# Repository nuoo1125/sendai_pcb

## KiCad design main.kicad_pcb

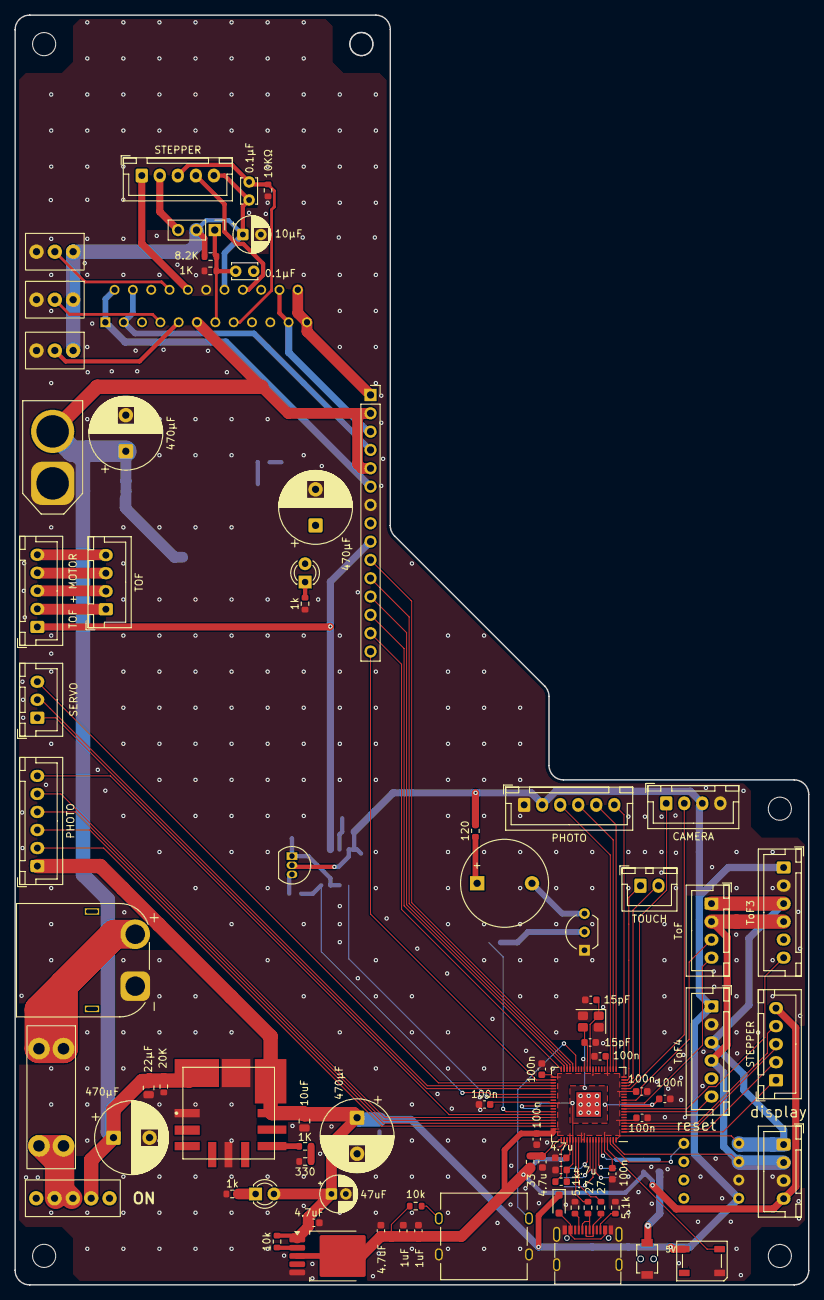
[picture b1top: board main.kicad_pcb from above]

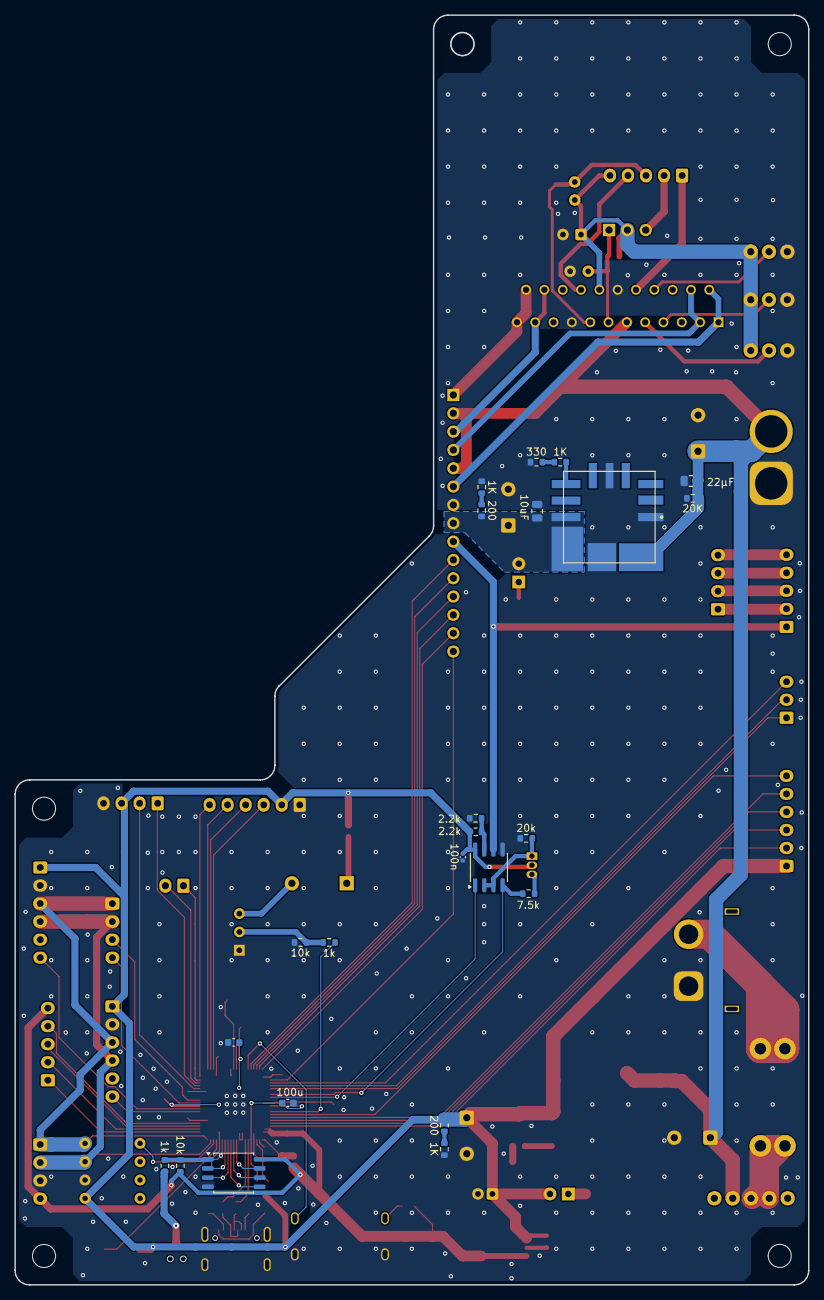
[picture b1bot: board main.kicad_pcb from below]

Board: 2 copper layers, 110.0 x 176.0 mm, 105 parts (23 on the bottom side), 97 nets.

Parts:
1K: 1K; R_0603_1608Metric
330: 330; R_0603_1608Metric
BZ1: UDB-05LFPN; Buzzer_12x9.5RM7.6
C1: 47uF; CP_Radial_D5.0mm_P2.00mm
C2, C3, C18, C19: 470μF; CP_Radial_D10.0mm_P5.00mm
C4, C8: 0.1μF; C_Disc_D3.4mm_W2.1mm_P2.50mm
C5, C9: 4.7uF; C_0603_1608Metric
C6, C7: 22μF; C_0805_2012Metric
C10, C13: 1uF; C_0603_1608Metric
C11: 100n; C_0402_1005Metric
C12: 10μF; CP_Radial_D5.0mm_P2.50mm
C14, C17, C20, C21: 4.7u; C_0603_1608Metric
C15, C16: 10uF; C_0805_2012Metric
C22, C23: 15pF; C_0603_1608Metric
C24: 100u; C_0603_1608Metric
C25, C26, C27, C28, C29, C30, C31, C32: 100n; C_0603_1608Metric
D1: CUHS20S30; D_SOD-323_HandSoldering
D2, D4: LED; LED_D3.0mm
D3: WS2812B; LED_WS2812B_PLCC4_5.0x5.0mm_P3.2mm
F1: Fuse; 3557-15_fuseholder
J1: Conn_01x02_Pin; AMASS_XT60PW-M_1x02_P7.20mm_Horizontal
J2: RP2350; USB_C
J5: Conn_01x04; JST_XH_B4B-XH-A_1x04_P2.50mm_Vertical
J6: ToF3; JST_XH_B6B-XH-A_1x06_P2.50mm_Vertical
J7: ToF4; JST_XH_B6B-XH-A_1x06_P2.50mm_Vertical
J8: ToF; JST_XH_B4B-XH-A_1x04_P2.50mm_Vertical
J9: gyro; bno055
J10: TOUCH; JST_XH_B2B-XH-A_1x02_P2.50mm_Vertical
J11, J12: PHOTO; JST_XH_B6B-XH-A_1x06_P2.50mm_Vertical
J15: Conn_01x02_Pin; AMASS_XT60-M_1x02_P7.20mm_Vertical
J16: TOF; JST_XH_B4B-XH-A_1x04_P2.50mm_Vertical
J17: CAMERA; JST_XH_B4B-XH-A_1x04_P2.50mm_Vertical
J18: Conn_01x15; PinSocket_1x15_P2.54mm_Vertical
L1: MBKK1608T3R3M; L_0603_1608Metric
MD1, MD2: OKL-T_6-W12N-C; MURATA_OKL-T-6-W12N-C_0
Q1: 2SA1015; TO-92_Inline
Q2: 2SC1815; PinHeader_1x03_P2.54mm_Vertical
Q3: 2N7000; TO-92_Inline_Wide
R1: 7.5k; R_0603_1608Metric
R2: 20k; R_0603_1608Metric
R3, R4: 5.1k; R_0603_1608Metric
R5, R6: 20K; R_0603_1608Metric
R7: 10KΩ; R_0603_1608Metric
R8, R10, R28, R31: 10k; R_0603_1608Metric
R9, R11, R27, R30: 1k; R_0603_1608Metric
R12: 8.2K; R_0603_1608Metric
R13, R16, R22, R23: 1K; R_0603_1608Metric
R14, R15: 2.2k; R_0603_1608Metric
R18: 330; R_0603_1608Metric
R20, R21: 200; R_0603_1608Metric
R24: 33; R_0603_1608Metric
R25, R26: 27; R_0603_1608Metric
R29: 120; R_0603_1608Metric
SERVO: Conn_01x03; JST_XH_B3B-XH-A_1x03_P2.50mm_Vertical
STEPPER: Conn_01x05; JST_XH_B5B-XH-A_1x05_P2.50mm_Vertical
STEPPER#2: Conn_01x05; JST_XH_B5B-XH-A_1x05_P2.50mm_Vertical
SW1: SW_SPDT; toggleswitch_tuyo
SW2: Boot_2350; TVAF06-A020B-R
SW3: SW_Push; takuto_sw
SW4, SW5, SW6: SW_SPDT; toggleswitch
TOF + MOTOR: Conn_01x05; JST_XH_B5B-XH-A_1x05_P2.50mm_Vertical
U1: NJM2819; TO-252-5_TabPin3
U2: MAX485ED; SOIC-8_3.9x4.9mm_P1.27mm
U3: W25Q128JVS; SOIC-8_5.3x5.3mm_P1.27mm
U4: SLA7078MPRT; sla7078
U5: RP2350_80QFN; RP2350-QFN-80-1EP_10x10_P0.4mm_EP3.4x3.4mm_ThermalVias
Y1: Crystal_GND24; Crystal_SMD_SeikoEpson_FA238-4Pin_3.2x2.5mm

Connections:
3.3V: C9.1, C10.1, C13.1, C14.1, C26.1, C27.1, C28.1, C29.1, C30.1, C31.1, C32.1, J5.4, R10.2, R24.1, R31.1, STEPPER#2.5, U1.3 (VOUT), U3.8 (VCC), U5.5 (IOVDD), U5.15 (IOVDD), U5.24 (IOVDD), U5.29 (IOVDD), U5.41 (IOVDD), U5.50 (IOVDD), U5.59 (ADC_AVDD), U5.60 (IOVDD), U5.64 (VREG_VIN), U5.68 (USB_OTP_VDD), U5.69 (QSPI_IOVDD), U5.76 (IOVDD)
3.3V_: C8.1, C12.1, Q2.2 (C), R12.1, STEPPER.5, SW4.1 (A), SW5.1 (A), SW6.1 (A), U4.14 (VDD)
+1V1: C17.1, C20.1, C24.1, C25.1, L1.1, U5.10 (DVDD), U5.32 (DVDD), U5.51 (DVDD), U5.65 (VREG_FB)
+5V: C1.1, C5.1, C11.1, C15.1, C18.1, D1.1 (K), D2.2 (A), D3.1 (VDD), J6.1, J7.1, J9.1, J11.2, J12.1, J17.3, MD1.4 (VOUT), MD1.5 (SENSE), Q1.2 (C), R8.1, R15.1, R20.1, R29.1, U1.1 (VIN), U2.8 (VCC)
+5VA: C16.1, C19.1, D4.2 (A), J18.8, MD2.4 (VOUT), MD2.5 (SENSE), R21.1
A: J18.6, U4.1 (OUTA), U4.2 (OUTA)
A_: J18.4, U4.3 (~OUTA), U4.4 (~OUTA)
B: J18.1, U4.22 (OUTB), U4.23 (OUTB)
B_: J18.3, U4.20 (~OUTB), U4.21 (~OUTB)
CS_2350: R9.2, R10.1, U3.1 (~CS), U5.75 (QSPI_SS)
DM_2350: J2.A7 (D-), J2.B7 (D-), R26.2
DP_2350: J2.A6 (D+), J2.B6 (D+), R25.2
GND: 330.1, C1.2, C2.2, C3.2, C4.2, C5.2, C6.2, C7.2, C9.2, C10.2, C11.2, C12.2, C13.2, C14.2, C15.2, C16.2, C17.2, C18.2, C19.2, C20.2, C21.2, C22.1, C23.1, C24.2, C25.2, C26.2, C27.2, C28.2, C29.2, C30.2, C31.2, C32.2, D3.3 (VSS), J1.1, J2.A1 (GND), J2.A12 (GND), J2.B1 (GND), J2.B12 (GND), J2.S1 (SHIELD), J5.3, J6.2, J7.2, J9.2, J11.1, J15.1, J17.4, J18.7, MD1.1 (~ON/OFF_CONTROL), MD1.3 (1_GROUND), MD1.7 (2_GROUND), MD2.1 (~ON/OFF_CONTROL), MD2.3 (1_GROUND), MD2.7 (2_GROUND), Q3.1 (S), R2.2, R3.2, R4.2, R5.1, R6.1, R7.2, R11.2, R13.2, R14.1, R18.1, R22.2, R23.2, R28.1, R30.2, SW2.1 (A), SW3.1, SW4.3 (C), SW5.3 (C), SW6.3 (C), U1.5 (GND), U2.5 (GND), U3.4 (GND), U4.12 (GND), U4.17 (SYNC), U5.62 (VREG_PGND), U5.81 (GND), Y1.2, Y1.4
M1: SW4.2 (B), U4.7 (M1)
M2: SW5.2 (B), U4.8 (M2)
M3: SW6.2 (B), U4.9 (M3)
unnamed: BZ1.1 (+), R29.2
unnamed: BZ1.2 (-), Q3.3 (D)
unnamed: D1.2 (A), J2.A4 (VBUS), J2.A9 (VBUS), J2.B4 (VBUS), J2.B9 (VBUS)
unnamed: D2.1 (K), R11.1
unnamed: D4.1 (K), R30.1
unnamed: F1.1, J1.2
unnamed: J2.A5 (CC1), R3.1
unnamed: J2.B5 (CC2), R4.1
unnamed: MD1.6 (TRIM), R16.2
unnamed: 1K.2, MD2.6 (TRIM)
unnamed: Q1.3 (B), R1.1
unnamed: Q1.1 (E), R2.1, U2.2 (~RE), U2.3 (DE)
unnamed: Q3.2 (G), R27.2, R28.2
unnamed: R16.1, R18.2
unnamed: 1K.1, 330.2
unnamed: R20.2, R22.1
unnamed: R21.2, R23.1
unnamed: F1.2, SW1.1 (A), SW1.2 (B)
unnamed: R9.1, SW2.2 (B)
unnamed: R8.2, U1.2 (CON)
unnamed: R14.2, R15.2, U2.7 (B)
unnamed: R31.2, SW3.2, U5.35 (RUN)
unnamed: R26.1, U5.66 (USB_DM)
unnamed: R25.1, U5.67 (USB_DP)
unnamed: C21.1, R24.2, U5.61 (VREG_AVDD)
unnamed: L1.2, U5.63 (VREG_LX)
unnamed: C22.2, U5.30 (XIN), Y1.1
unnamed: C23.2, U5.31 (XOUT), Y1.3
SCLK_2350: U3.6 (CLK), U5.71 (QSPI_SCLK)
SD0_2350: U3.5 (DI/IO_{0}), U5.72 (QSPI_SD0)
SD1_2350: U3.2 (DO/IO_{1}), U5.74 (QSPI_SD1)
SD2_2350: U3.3 (~WP/IO_{2}), U5.73 (QSPI_SD2)
SD3_2350: U3.7 (~HOLD/~RESET/IO_{3}), U5.70 (QSPI_SD3)
VCC: C2.1, C3.1, C6.1, C7.1, J15.2, J18.2, J18.5, MD1.2 (VIN), MD2.2 (VIN), R5.2, R6.2, SW1.3 (C), U4.11 (VBB)
buzaa: R27.1, U5.53 (GPIO42_ADC2)
camera_rx: J17.1, U5.17 (GPIO17)
camera_tx: J17.2, U5.16 (GPIO16)
clock: STEPPER#2.1, U5.1 (GPIO4)
clock_: STEPPER.1, U4.10 (CLOCK)
direction: STEPPER#2.4, U5.4 (GPIO7)
direction_: STEPPER.4, U4.16 (CW/CCW)
display_scl: J5.1, J6.3, J7.3, J8.1, J9.4, U5.80 (GPIO3)
display_sda: J5.2, J6.4, J7.4, J8.2, J9.3, U5.79 (GPIO2)
gyro_reset: J9.8, U5.78 (GPIO1)
ledfullcolor: D3.4 (DIN), U5.77 (GPIO0)
motor_rx: U2.1 (RO), U5.48 (GPIO39)
motor_serial: J18.9, TOF + MOTOR.1, U2.6 (A)
motor_tx: R1.2, U2.4 (DI), U5.47 (GPIO38)
obstacle_backward1: J12.6, U5.54 (GPIO43_ADC3)
obstacle_backward2: J12.5, U5.55 (GPIO44_ADC4)
obstacle_forward1: J10.2, U5.18 (GPIO18)
obstacle_forward2: J10.1, U5.19 (GPIO19)
photo_backward1: J12.4, U5.56 (GPIO45_ADC5)
photo_backward2: J12.3, U5.57 (GPIO46_ADC6)
photo_backward3: J12.2, U5.58 (GPIO47_ADC7)
photo_csn: J11.5, U5.21 (GPIO21)
photo_rx: J11.6, U5.20 (GPIO20)
photo_sck: J11.4, U5.22 (GPIO22)
photo_tx: J11.3, U5.23 (GPIO23)
reset: STEPPER#2.3, U5.3 (GPIO6)
reset_: C8.2, R7.1, STEPPER.3, U4.15 (RESET)
servo1: J18.15, U5.42 (GPIO33)
servo2: J18.14, U5.40 (GPIO32)
servo3: J18.13, U5.39 (GPIO31)
servo4: J18.12, U5.38 (GPIO30)
servo5: J18.11, U5.37 (GPIO29)
servo6: J18.10, U5.36 (GPIO28)
servo7: SERVO.3, U5.43 (GPIO34)
servo8: SERVO.2, U5.44 (GPIO35)
servo9: SERVO.1, U5.45 (GPIO36)
sleep: STEPPER#2.2, U5.2 (GPIO5)
sleep_: Q2.3 (B), STEPPER.2
sleepl: C4.1, Q2.1 (E), R12.2, R13.1, U4.13 (REF/SLEEP1)
tof_scl_s: J16.1, TOF + MOTOR.2
tof_sda_s: J16.2, TOF + MOTOR.3
xshut1: J8.4, U5.11 (GPIO12)
xshut1_s: J16.4, TOF + MOTOR.5
xshut2: J8.3, U5.12 (GPIO13)
xshut2_s: J16.3, TOF + MOTOR.4
xshut3: J6.6, U5.9 (GPIO11)
xshut4: J7.6, U5.8 (GPIO10)
